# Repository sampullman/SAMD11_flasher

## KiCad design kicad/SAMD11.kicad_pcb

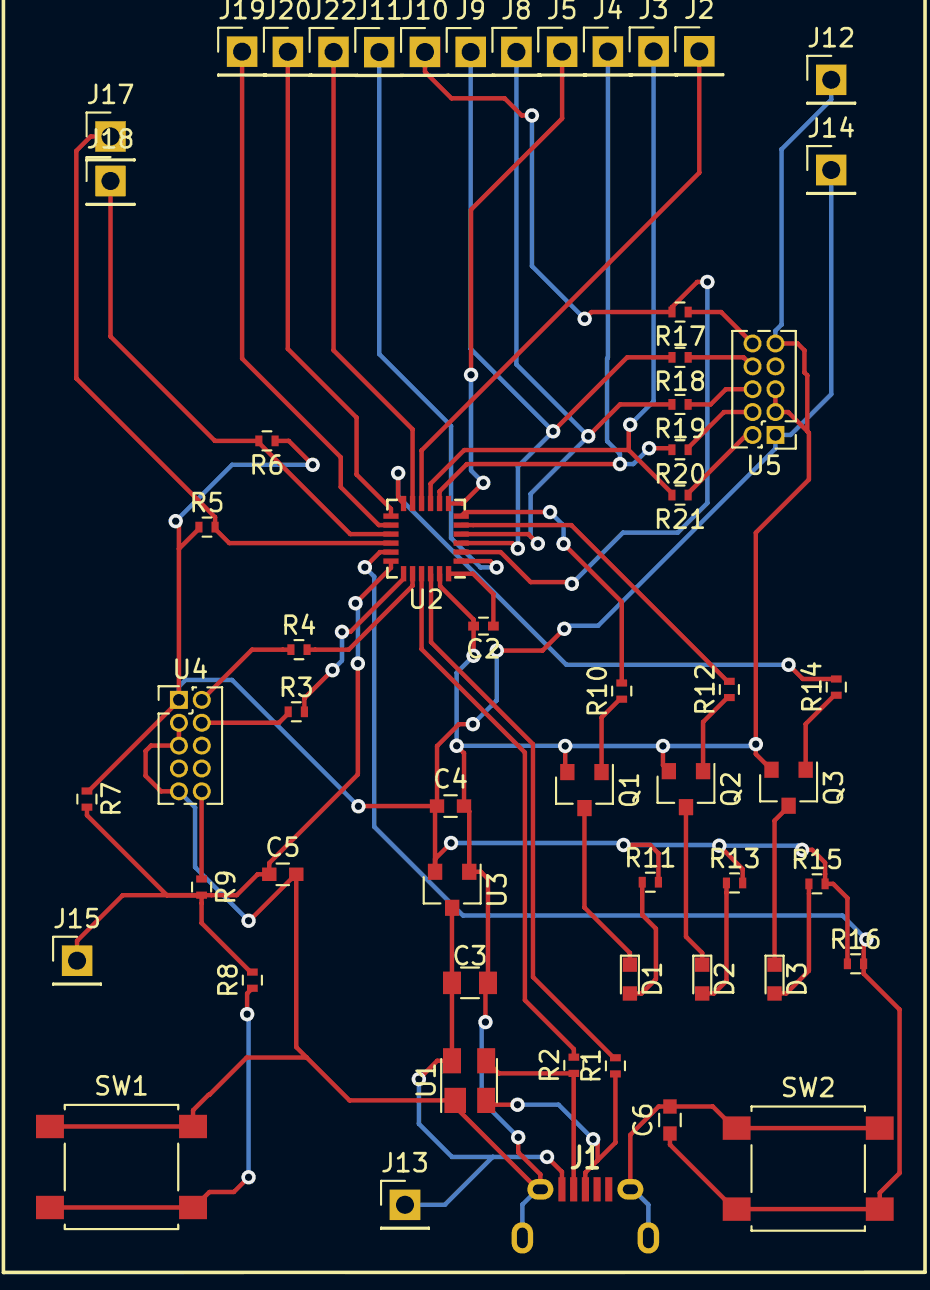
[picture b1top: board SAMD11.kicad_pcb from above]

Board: 2 copper layers, 57 parts (0 on the bottom side), 45 nets.

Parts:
C2: 0.1uF; C_0402
C3: 10uF; C_0805
C4, C5, C6: 1uF; C_0603
D1, D2: LED_GREEN; LED_0603
D3: LED_RED; LED_0603
J1: USB_OTG; FCI_10118194-0001LF
J2: CONN_PA11; Pin_Header_Straight_1x01_Pitch2.54mm
J3: CONN_PA10; Pin_Header_Straight_1x01_Pitch2.54mm
J4: CONN_PA09; Pin_Header_Straight_1x01_Pitch2.54mm
J5: CONN_PA08; Pin_Header_Straight_1x01_Pitch2.54mm
J8: CONN_PA05; Pin_Header_Straight_1x01_Pitch2.54mm
J9: CONN_PA04; Pin_Header_Straight_1x01_Pitch2.54mm
J10: CONN_PA03; Pin_Header_Straight_1x01_Pitch2.54mm
J11: CONN_PA02; Pin_Header_Straight_1x01_Pitch2.54mm
J12: CONN_GND; Pin_Header_Straight_1x01_Pitch2.54mm
J13: CONN_5V; Pin_Header_Straight_1x01_Pitch2.54mm
J14: CONN_3V; Pin_Header_Straight_1x01_Pitch2.54mm
J15: CONN_RST; Pin_Header_Straight_1x01_Pitch2.54mm
J17: CONN_PA23; Pin_Header_Straight_1x01_Pitch2.54mm
J18: CONN_PA22; Pin_Header_Straight_1x01_Pitch2.54mm
J19: CONN_PA17; Pin_Header_Straight_1x01_Pitch2.54mm
J20: CONN_PA16; Pin_Header_Straight_1x01_Pitch2.54mm
J22: CONN_PA14; Pin_Header_Straight_1x01_Pitch2.54mm
Q1, Q2, Q3: MMBT3904; SOT-23
R1, R2, R3, R4, R17, R18, R19, R20, R21: 0; R_0402
R5, R6, R7, R10, R12, R14, R16: 10K; R_0402
R8, R9: 39; R_0402
R11, R13, R15: 680; R_0402
SW1: SW_RESET; SW_SPST_B3S-1000
SW2: SW_USR; SW_SPST_B3S-1000
U1: PRTR5V0U2X; SOT-143
U2: ATSAMD11D14A-MNT; QFN-24_4x4mm_Pitch0.5mm
U3: AP2127N-3.3; SOT-23
U4, U5: SWD_2x5; Pin_Header_Straight_2x05_Pitch1.27mm

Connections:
+3V3: C2.1, C4.1, J14.1, R5.1, R6.1, R7.1, R11.2, R13.2, R15.2, R16.1, U2.24, U3.2, U4.1, U5.1
+5V: C3.1, J1.1, J13.1, U1.4, U3.3
AT_PA02: J11.1, U2.1
AT_PA03: J10.1, R17.2, U2.2
AT_PA04: J9.1, R18.2, U2.3
AT_PA05: J8.1, R19.2, U2.4
AT_PA06: R12.2, U2.5
AT_PA07: R10.2, U2.6
AT_PA08: J5.1, U2.7
AT_PA09: J4.1, R20.2, U2.8
AT_PA10: J3.1, R21.2, U2.9
AT_PA11: J2.1, U2.10
AT_PA14: J22.1, U2.11
AT_PA15: R14.2, U2.12
AT_PA16: J20.1, U2.13
AT_PA17: J19.1, U2.14
AT_PA22: J18.1, R6.2, U2.15
AT_PA23: J17.1, R5.2, U2.16
AT_PA27: C6.1, R16.2, SW2.2, U2.17
AT_RST: C5.1, J15.1, R7.2, R8.2, R9.2, U2.18
GND: C2.2, C3.2, C4.2, C5.2, C6.2, J1.5, J1.6, J12.1, Q1.2, Q2.2, Q3.2, SW1.1, SW2.1, U1.1, U2.23, U3.1, U4.3, U4.5, U4.9, U5.3, U5.5, U5.9
unnamed: D1.1, Q1.3
unnamed: D1.2, R11.1
unnamed: D2.1, Q2.3
unnamed: D2.2, R13.1
unnamed: D3.1, Q3.3
unnamed: D3.2, R15.1
unnamed: J1.2, R2.1, U1.3
unnamed: J1.3, R1.1, U1.2
unnamed: Q1.1, R10.1
unnamed: Q2.1, R12.1
unnamed: Q3.1, R14.1
unnamed: R1.2, U2.22
unnamed: R2.2, U2.21
unnamed: R3.1, U4.4
unnamed: R3.2, U2.19
unnamed: R4.1, U4.2
unnamed: R4.2, U2.20
unnamed: R8.1, SW1.2
unnamed: R17.1, U5.10
unnamed: R18.1, U5.8
unnamed: R19.1, U5.6
unnamed: R20.1, U5.4
unnamed: R21.1, U5.2
SWD_RST: R9.1, U4.10

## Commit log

2017-10-23 Schematic done, board started
2017-10-23 Finished preliminary board layout
